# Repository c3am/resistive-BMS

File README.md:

This is a low cost 4s BMS (battery management system) based on the ch32v003 microcontroller.
features:
- Cell voltage measurement using an ads1115 16bit adc
- high side bidirectional current sensing using the ina181a2 current sense amplifier
- charge/discharge enable using low side mosfets
- 20Ohm resistive balancing (-> 200mA at 4V -> 0.8W)
- I/O: 1x Uart, 1x SWIO (for programming)

This BMS is still under development and I haven't even tested it yet.

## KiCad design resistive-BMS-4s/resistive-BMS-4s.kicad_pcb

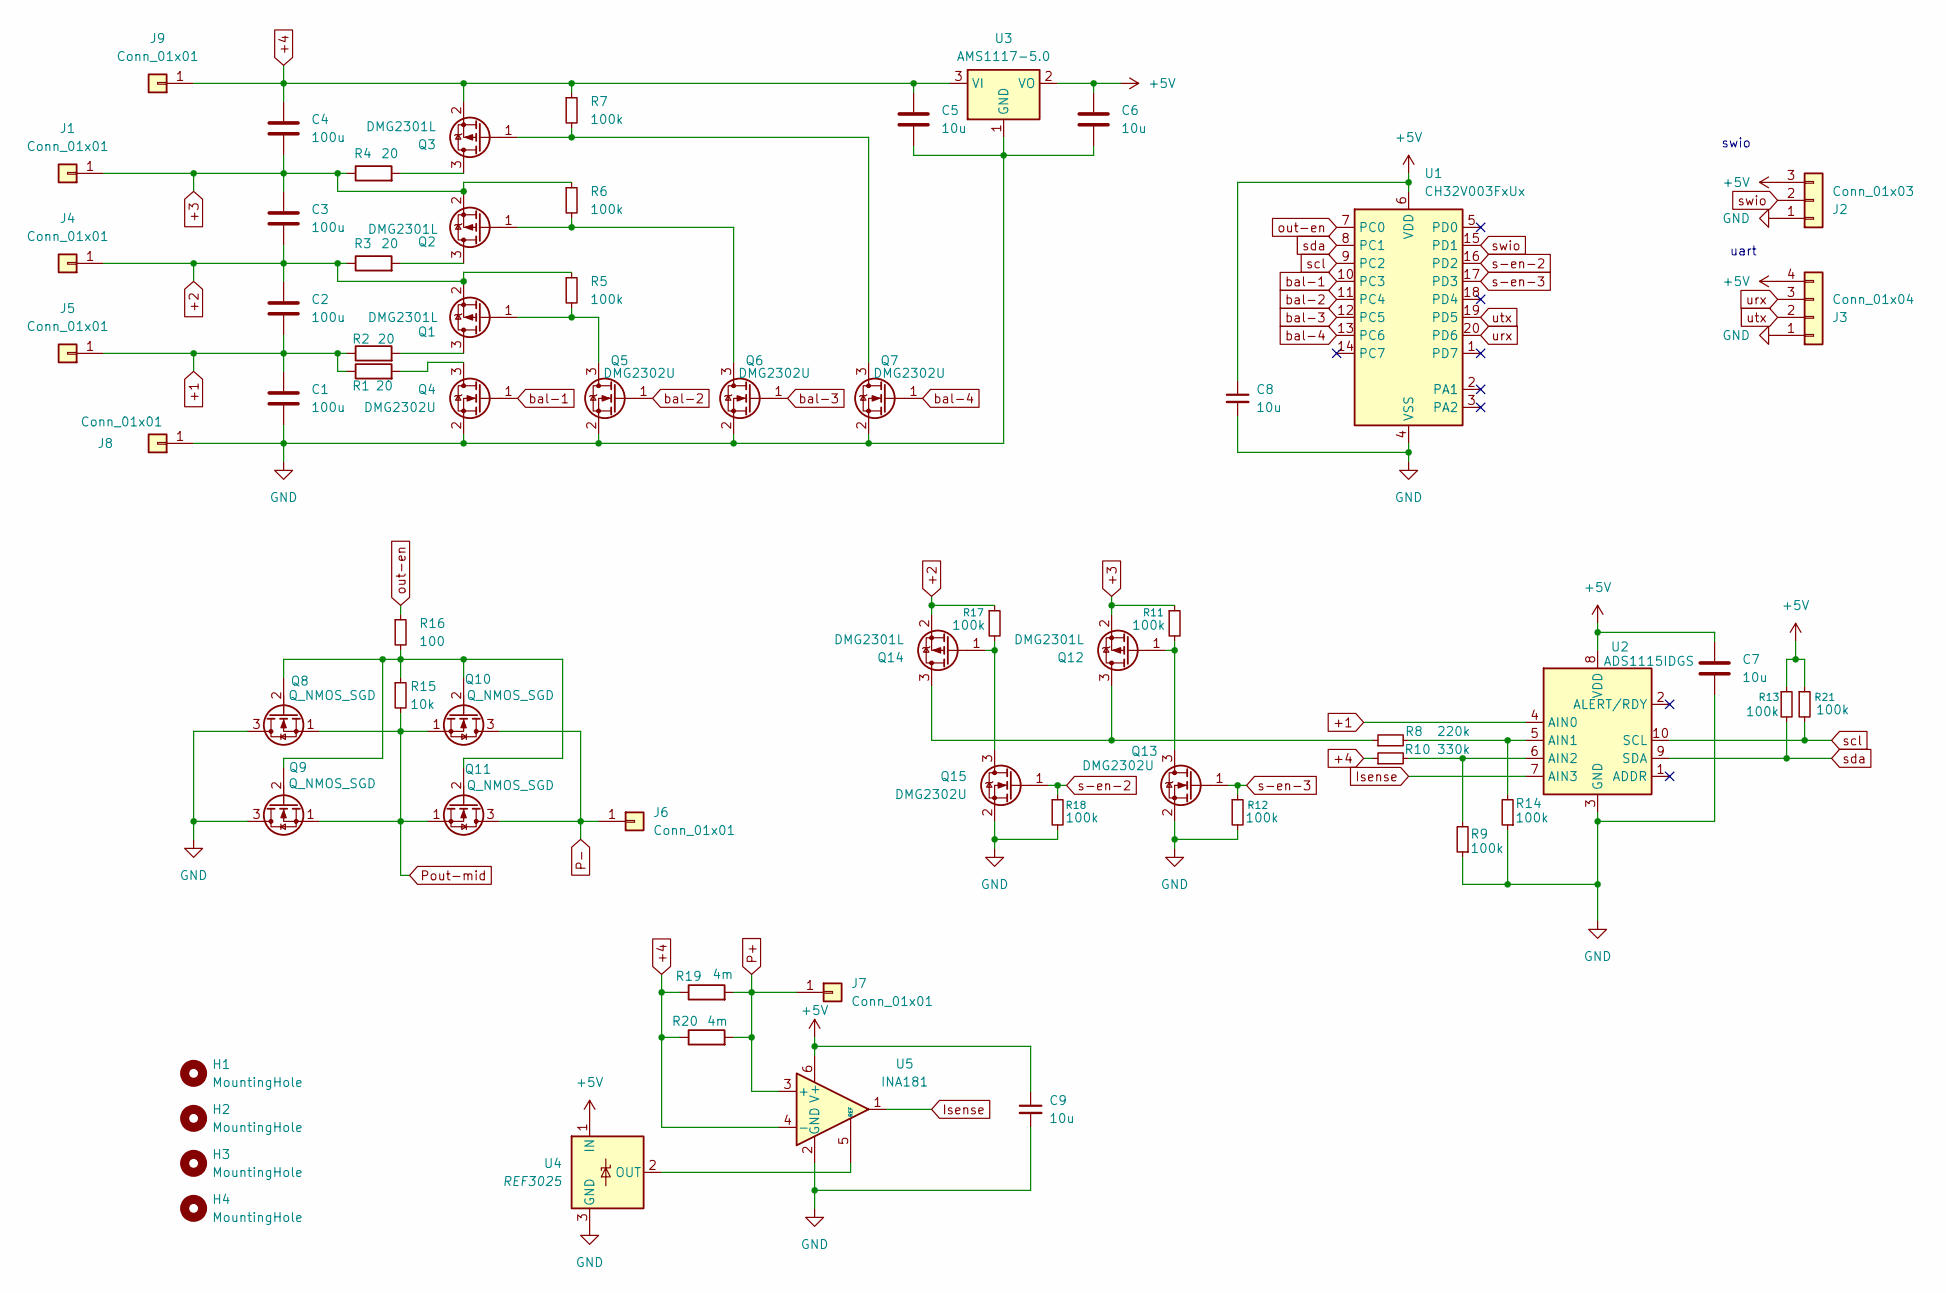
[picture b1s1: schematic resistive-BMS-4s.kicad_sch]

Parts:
C1, C2, C3, C4: 100u; C_1206_3216Metric
C5, C6, C7, C8, C9: 10u; C_0603_1608Metric
H1, H2, H3, H4: MountingHole; MountingHole_3.2mm_M3
J1, J4, J5: Conn_01x01; pad-4x3mm
J2: Conn_01x03; PinHeader_1x03_P2.54mm_Vertical
J3: Conn_01x04; PinHeader_1x04_P2.54mm_Vertical
J6, J7, J8, J9: Conn_01x01; pad-6x6mm
Q1, Q2, Q3, Q12, Q14: DMG2301L; SOT-23
Q4, Q5, Q6, Q7, Q13, Q15: DMG2302U; SOT-23
Q8, Q9, Q10, Q11: Q_NMOS_SGD; PQFN-8-EP_6x5mm_P1.27mm_Generic
R1, R2, R3, R4: 20; R_2512_6332Metric
R5, R6, R7, R9, R11, R12, R13, R14, R17, R18, R21: 100k; R_0603_1608Metric
R8: 220k; R_0603_1608Metric
R10: 330k; R_0603_1608Metric
R15: 10k; R_0603_1608Metric
R16: 100; R_0603_1608Metric
R19, R20: 4m; R_2512_6332Metric
U1: CH32V003FxUx; QFN-20-1EP_3x3mm_P0.4mm_EP1.65x1.65mm
U2: ADS1115IDGS; TSSOP-10_3x3mm_P0.5mm
U3: AMS1117-5.0; SOT-223-3_TabPin2
U4: REF3025; SOT-23
U5: INA181; SOT-23-6

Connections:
+1: C1.1, C2.2, J5.1, R1.1, R2.1, U2.4 (AIN0)
+2: C2.1, C3.2, J4.1, Q1.2 (S), Q14.2 (S), R3.1, R5.1, R17.1
+3: C3.1, C4.2, J1.1, Q2.2 (S), Q12.2 (S), R4.1, R6.1, R11.1
+4: C4.1, C5.1, J9.1, Q3.2 (S), R7.1, R10.1, R19.1, R20.1, U3.3 (VI), U5.4 (-)
+5V: C6.1, C7.1, C8.1, C9.1, J2.3, J3.4, R13.1, R21.1, U1.6 (VDD), U2.8 (VDD), U3.2 (VO), U4.1 (IN), U5.6 (V+)
GND: C1.2, C5.2, C6.2, C7.2, C8.2, C9.2, J2.1, J3.1, J8.1, Q4.2 (S), Q5.2 (S), Q6.2 (S), Q7.2 (S), Q8.3 (D), Q9.3 (D), Q13.2 (S), Q15.2 (S), R9.1, R12.2, R14.1, R18.2, U1.4 (VSS), U1.21 (VSS), U2.3 (GND), U3.1 (GND), U4.3 (GND), U5.2 (GND)
Isense: U2.7 (AIN3), U5.1
unnamed: Q1.3 (D), R2.2
unnamed: Q1.1 (G), Q5.3 (D), R5.2
unnamed: Q2.3 (D), R3.2
unnamed: Q2.1 (G), Q6.3 (D), R6.2
unnamed: Q3.3 (D), R4.2
unnamed: Q3.1 (G), Q7.3 (D), R7.2
unnamed: Q4.3 (D), R1.2
unnamed: Q8.2 (G), Q9.2 (G), Q10.2 (G), Q11.2 (G), R15.1, R16.2
unnamed: Q12.3 (D), Q14.3 (D), R8.1
unnamed: Q12.1 (G), Q13.3 (D), R11.2
unnamed: Q14.1 (G), Q15.3 (D), R17.2
unnamed: R8.2, R14.2, U2.5 (AIN1)
unnamed: R9.2, R10.2, U2.6 (AIN2)
unnamed: U4.2 (OUT), U5.5 (REF)
P+: J7.1, R19.2, R20.2, U5.3 (+)
P-: J6.1, Q10.3 (D), Q11.3 (D)
Pout-mid: Q8.1 (S), Q9.1 (S), Q10.1 (S), Q11.1 (S), R15.2
bal-1: Q4.1 (G), U1.10 (PC3)
bal-2: Q5.1 (G), U1.11 (PC4)
bal-3: Q6.1 (G), U1.12 (PC5)
bal-4: Q7.1 (G), U1.13 (PC6)
out-en: R16.1, U1.7 (PC0)
s-en-2: Q15.1 (G), R18.1, U1.16 (PD2)
s-en-3: Q13.1 (G), R12.1, U1.17 (PD3)
scl: R21.2, U1.9 (PC2), U2.10 (SCL)
sda: R13.2, U1.8 (PC1), U2.9 (SDA)
swio: J2.2, U1.15 (PD1)
urx: J3.3, U1.20 (PD6)
utx: J3.2, U1.19 (PD5)

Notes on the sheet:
uart
swio

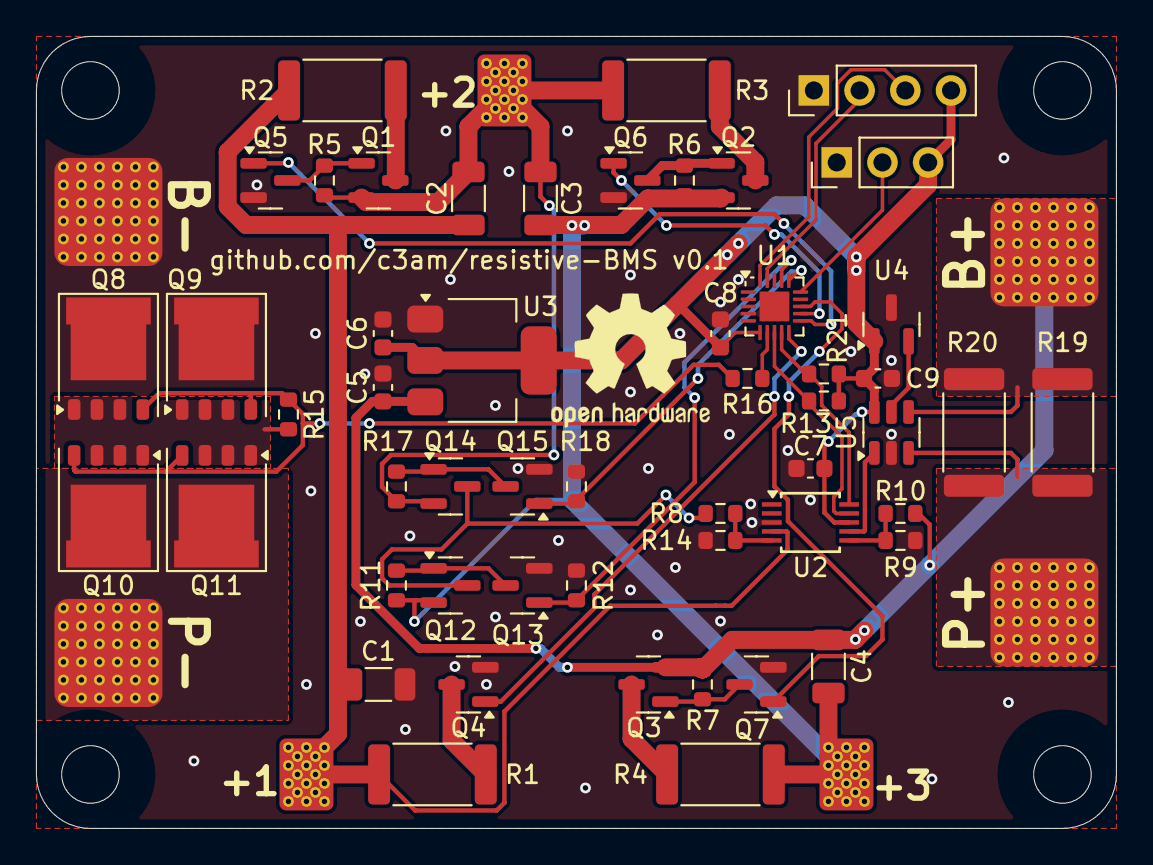
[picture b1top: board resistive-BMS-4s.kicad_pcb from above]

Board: 2 copper layers, 60.0 x 44.0 mm, 63 parts (0 on the bottom side), 36 nets.

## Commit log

2025-04-23 commit without unnecessary files
2025-04-23 readme added
2025-04-23 readme.md renamed to README.md
2025-04-23 added images
2025-04-23 added value to decoupling capacitor
2025-04-23 added silkscreen labels to pads
2025-05-07 version 0.1
2025-05-07 added fabrication output files
